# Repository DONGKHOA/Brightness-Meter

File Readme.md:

# BRIGHTNESS METER
## Yêu cầu hệ thống
- Thiết kế máy đo độ rọi ánh sáng sử dụng LDR: có 2 thang đo
  - Thang 1: tầm đo 10-100lux, độ phân giải 1lux
  - Thang 2: tầm đo 10-1000lux, độ phân giải 10lux
  - Màn hình hiển thị LCD giá trị đo được, có nút nhấn để thay đổi giữa 2 thang đo
  - Mạch cho phép cài đặt giá trị ngưỡng độ rọi thông qua LCD và nút nhấn. Nếu độ rọi đặt vào máy đo lớn hơn giá trị cài đặt, báo đỏ LED.

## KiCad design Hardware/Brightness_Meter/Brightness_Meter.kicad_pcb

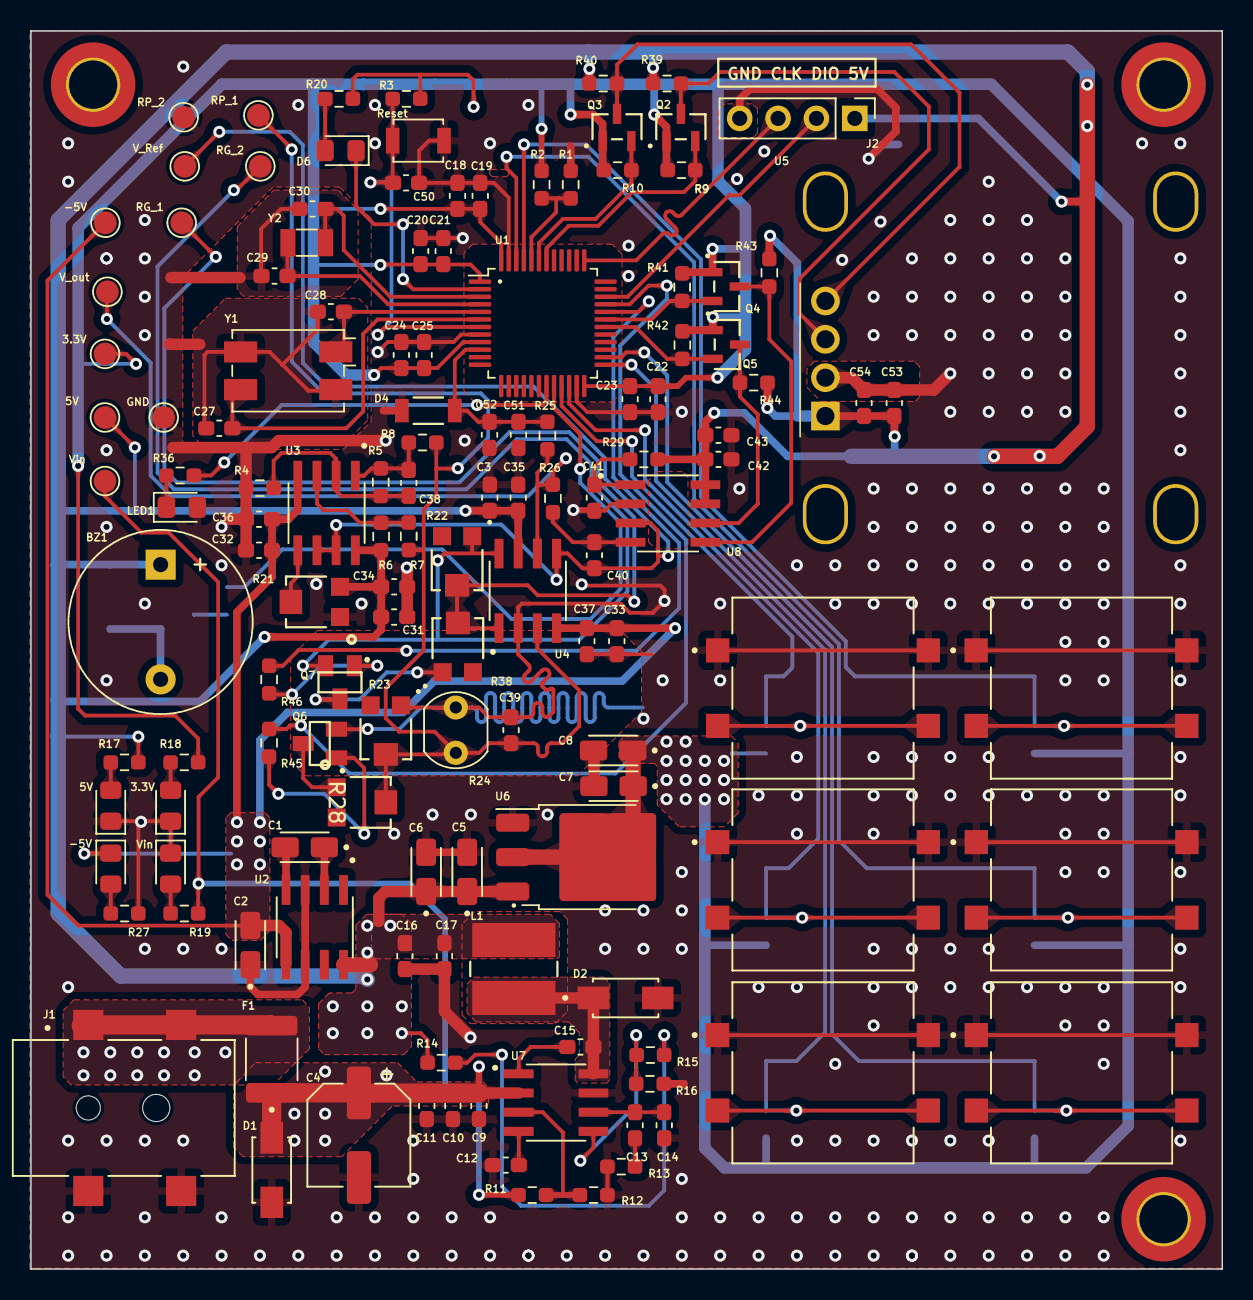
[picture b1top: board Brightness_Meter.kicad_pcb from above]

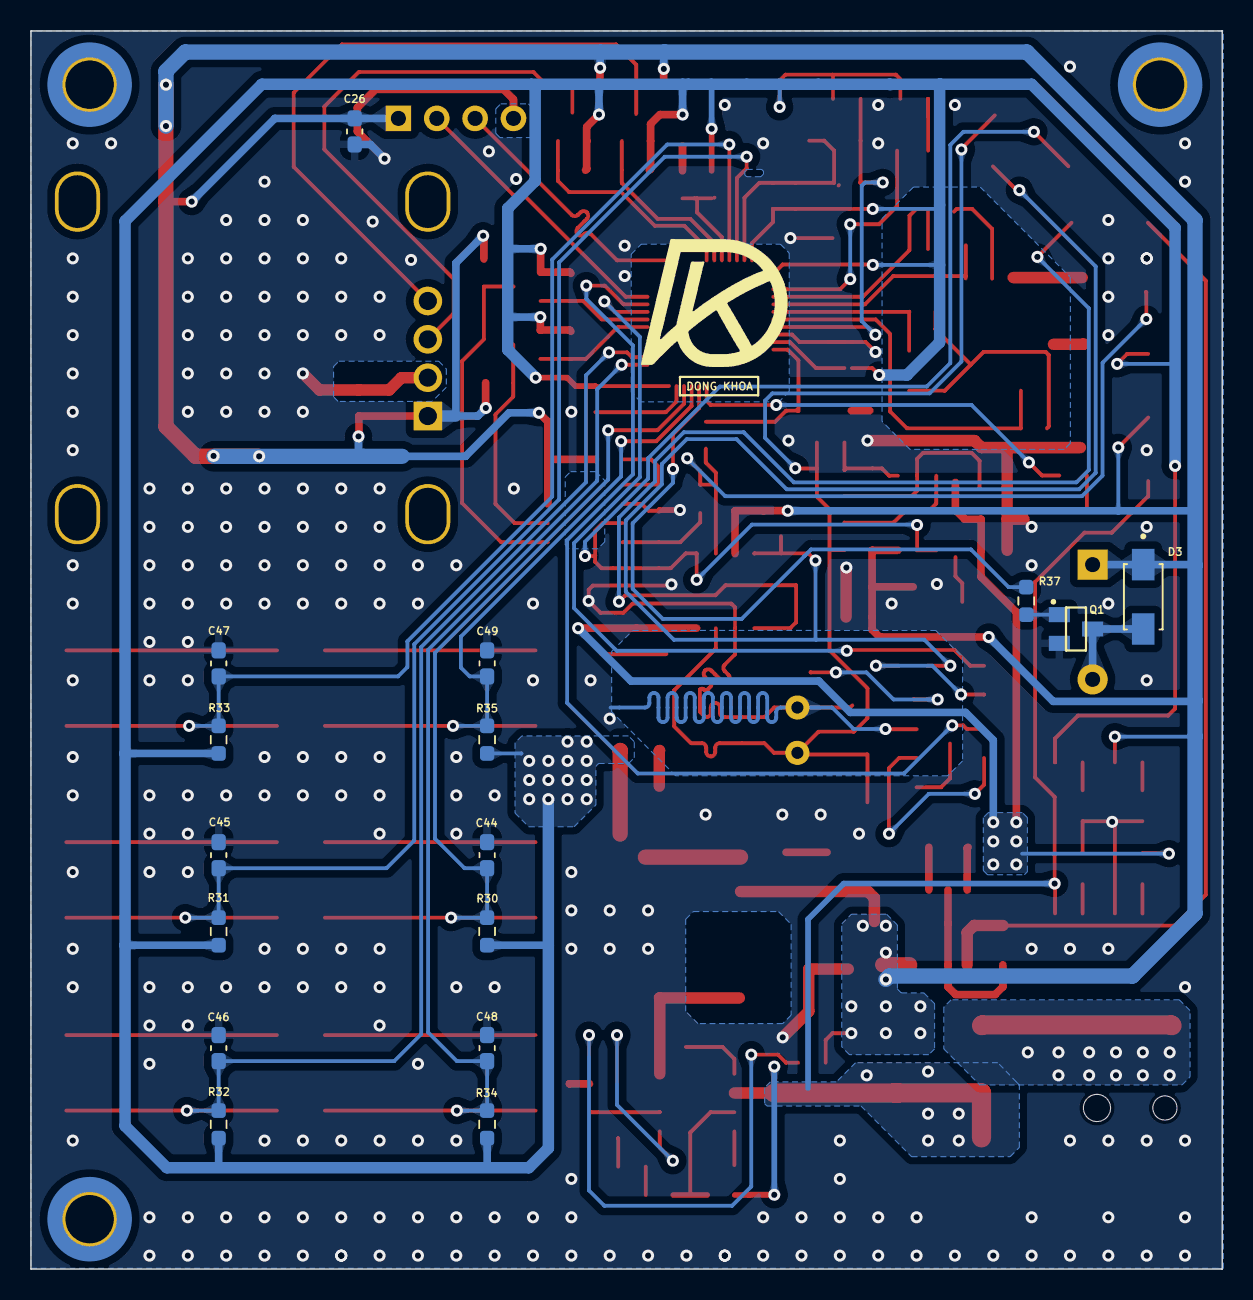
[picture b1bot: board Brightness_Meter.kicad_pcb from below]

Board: 2 copper layers, 78.9 x 82.0 mm, 153 parts (16 on the bottom side), 67 nets.

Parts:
3.3V: 3.3V; TestPoint_Pad_D1.5mm
3.3V#2, 5V#2: BLUE; LED_0805_2012Metric_Pad1.15x1.40mm_HandSolder
5V: 5V; TestPoint_Pad_D1.5mm
-5V: -5V; TestPoint_Pad_D1.5mm
-5V#2: BLUE; LED_0805_2012Metric_Pad1.15x1.40mm_HandSolder
BZ1: Buzzer; Buzzer_12x9.5RM7.6
C1, C2, C6, C7: 10uF/16V; CAPMP3216X180N
C3, C26, C31, C32, C33, C51: 10uF/16V; C_0603_1608Metric_Pad1.08x0.95mm_HandSolder
C4: 22uF/25V; CP_Elec_6.3x5.4
C5, C8: 1uF/25V; CAPMP3216X180N
C9, C10: 4.7uF/25V; C_0603_1608Metric_Pad1.08x0.95mm_HandSolder
C11, C12, C25: 10nF/50V; C_0603_1608Metric_Pad1.08x0.95mm_HandSolder
C13: 1nF/50V; C_0603_1608Metric_Pad1.08x0.95mm_HandSolder
C14: 47pF/50V; C_0603_1608Metric_Pad1.08x0.95mm_HandSolder
C15: 0.1uF/16V; C_0603_1608Metric_Pad1.08x0.95mm_HandSolder
C16, C17: 47uF/6.3V; C_0603_1608Metric_Pad1.08x0.95mm_HandSolder
C18, C20, C22: 4.7uF/10V; C_0603_1608Metric_Pad1.08x0.95mm_HandSolder
C19, C21, C23, C34, C35, C36, C37, C44, C45, C46, C47, C48, C49, C50, C52: 100nF/16V; C_0603_1608Metric_Pad1.08x0.95mm_HandSolder
C24, C39: 1uF/16V; C_0603_1608Metric_Pad1.08x0.95mm_HandSolder
C27, C28, C29, C30: 20pF/50V; C_0603_1608Metric_Pad1.08x0.95mm_HandSolder
C38: 10pF/50V; C_0603_1608Metric_Pad1.08x0.95mm_HandSolder
C40, C41, C43, C54: 100nF/50V; C_0603_1608Metric_Pad1.08x0.95mm_HandSolder
C42, C53: 10uF/6.3V; C_0603_1608Metric_Pad1.08x0.95mm_HandSolder
D1, D2, D3: SS34; DIOM4325X250N
D4: ZMM3V3; ZDO_ZMM_3p5x1p45_STM
D6: Led_test; LED_0805_2012Metric_Pad1.15x1.40mm_HandSolder
DOWN1: DOWN; SW_TL3300CF260Q
F1: Fuse_Small; Fuse_1812_4532Metric_Pad1.30x3.40mm_HandSolder
GND: GND; TestPoint_Pad_D1.5mm
H1, H2, H3: MountingHole; MountingHole_3.2mm_M3_DIN965_Pad_TopBottom
J1: JACK-DC; SPARKFUN_PRT-12748
J2: Load Program; PinHeader_1x04_P2.54mm_Vertical
L1: 6.8uH/2.2A; IND_SDE0604A_5P8X5P2X4P5_BRN
LED1: RED; LED_0805_2012Metric_Pad1.15x1.40mm_HandSolder
LEFT1: LEFT; SW_TL3300CF260Q
MODE1: MODE; SW_TL3300CF260Q
Q1, Q6, Q7: MMBT2222A; SOT23
Q2, Q3, Q4, Q5: BSN20; SOT23_NEX
R1, R2, R25, R26: 0/1%; R_0603_1608Metric_Pad0.98x0.95mm_HandSolder
R3, R9, R10, R16, R30, R31, R32, R33, R34, R35, R39, R40, R41, R42, R43, R44: 10k/1%; R_0603_1608Metric_Pad0.98x0.95mm_HandSolder
R4, R5, R6, R7, R8: R_Small_US; R_0603_1608Metric_Pad0.98x0.95mm_HandSolder
R11: 330k/1%; R_0603_1608Metric_Pad0.98x0.95mm_HandSolder
R12: 47k/1%; R_0603_1608Metric_Pad0.98x0.95mm_HandSolder
R13: 30k/1%; R_0603_1608Metric_Pad0.98x0.95mm_HandSolder
R14: 2.49k/1%; R_0603_1608Metric_Pad0.98x0.95mm_HandSolder
R15: 49.9k/1%; R_0603_1608Metric_Pad0.98x0.95mm_HandSolder
R17, R18, R20, R36, R37, R45, R46: 1k/1%; R_0603_1608Metric_Pad0.98x0.95mm_HandSolder
R19, R27: 4.7k/1%; R_0603_1608Metric_Pad0.98x0.95mm_HandSolder
R21: EVM-3ESX50B14; EVM-3ESX50B14_PAN
R22, R23, R28, R38: EVM-3E; EVM-3ESX50B14_PAN
R24: GL5528; R_LDR_5.0x4.1mm_P3mm_Vertical
R29: 220/1%; R_0603_1608Metric_Pad0.98x0.95mm_HandSolder
RG_1, RG_2: RG; TestPoint_Pad_D1.5mm
RIGHT1: RIGHT; SW_TL3300CF260Q
RP_1, RP_2: RP; TestPoint_Pad_D1.5mm
Reset: SW_Push; SW_SPST_B3U-1000P
SET1: SET; SW_TL3300CF260Q
U1: STM32F030C8Tx; LQFP-48_7x7mm_P0.5mm
U2: ICL7662CPA; SOIC127P600X175-8N
U3: MCP6002; SOIC127P599X173-8N
U4: INA128; SOIC127P599X175-8N
U5: SSD1306
U6: LM1117DT-3.3; TO-252-3_TabPin2
U7: TPS54331D; SOIC127P599X175-8N
U8: HX710B
UP1: UP; SW_TL3300CF260Q
V_Ref: V_Ref; TestPoint_Pad_D1.5mm
V_out: V_out; TestPoint_Pad_D1.5mm
Vin: BLUE; LED_0805_2012Metric_Pad1.15x1.40mm_HandSolder
Vin#2: Vin; TestPoint_Pad_D1.5mm
Y1: 8MHz; Crystal_SMD_EuroQuartz_MQ-4Pin_7.0x5.0mm
Y2: 32.768KHz; Crystal_SMD_3215-2Pin_3.2x1.5mm

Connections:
+3.3V: 3.3V.1, C7.1, C8.1, C18.1, C19.1, C20.1, C21.1, C22.1, C23.1, C24.1, C25.1, Q2.1 (G), Q3.1 (G), Q4.1 (G), Q5.1 (G), R2.1, R3.1, R9.1, R10.1, R18.1, R20.1, R30.2, R31.2, R32.2, R33.2, R34.2, R35.2, R41.1, R42.1, U1.1 (VDD), U1.9 (VDDA), U1.24 (VDD), U1.48 (VDD), U6.2 (VO)
+5V: 5V.1, BZ1.1 (-), C3.1, C5.1, C6.1, C16.1, C17.1, C26.1, C31.1, C34.1, C35.1, C42.1, C43.1, C53.1, C54.1, D3.C, J2.1, L1.1, R6.2, R14.1, R17.1, R21.3, R29.2, R39.1, R40.1, R43.1, R44.1, U2.8 (V+), U3.8 (VDD), U4.7 (V+), U5.1 (vcc), U6.3 (VI), U8.7 (DVDD), U8.8 (AVDD)
-5V: -5V.1, -5V#2.1 (K), C2.2, C32.2, C33.2, C36.2, C37.2, U2.5 (VOUT), U3.4 (VSS), U4.4 (V-)
/MCU/BOOT0: R1.1, R2.2, U1.44 (BOOT0)
/MCU/LED_TEST: D6.1 (K), U1.2 (PC13)
/MCU/OSC32_IN: C30.1, U1.3 (PC14), Y2.1
/MCU/OSC32_OUT: C29.1, U1.4 (PC15), Y2.2
/MCU/OSC_IN: C28.1, U1.5 (PF0), Y1.1
/MCU/OSC_OUT: C27.1, U1.6 (PF1), Y1.3
/MCU/RESET: C50.2, R3.2, Reset.2, U1.7 (NRST)
/MCU/SWCLK: J2.3, U1.37 (PA14)
/MCU/SWDIO: J2.2, U1.34 (PA13)
/Power/Vin: C4.1, C9.1, C10.1, C11.1, D1.C, F1.2, R11.1, R19.1, U7.2 (VIN), Vin#2.1
/measure/CURRENT_SRC: C39.2, R7.1, R8.2, R23.2, R24.1, R28.2, RP_1.1, U4.3 (+)
/measure/vout: R25.2, R26.1, U4.6, V_out.1
ADC_CLK: Q4.2 (S), R41.2, U1.31 (PA10)
ADC_DATA: Q5.2 (S), R42.2, U1.30 (PA9)
ADC_HX71OB: C40.2, R26.2, U8.4 (INP)
ADC_INO: C51.1, C52.1, D4.1, R25.1, U1.10 (PA0)
BUZZER: R37.1, U1.20 (PB2)
CHANGE_GAIN: R46.2, U1.32 (PA11)
CHANGE_RESISTOR: R45.2, U1.33 (PA12)
CLK_HX710B: Q4.3 (D), R43.2, U8.5 (PD_SCK)
DATA_HX710B: Q5.3 (D), R44.2, U8.6 (DOUT)
GND: 3.3V#2.1 (K), 5V#2.1 (K), C2.1, C3.2, C4.2, C5.2, C6.2, C7.2, C8.2, C9.2, C10.2, C11.2, C12.2, C14.2, C16.2, C17.2, C18.2, C19.2, C20.2, C21.2, C22.2, C23.2, C24.2, C25.2, C26.2, C27.2, C28.2, C29.2, C30.2, C31.2, C32.1, C33.1, C34.2, C35.2, C36.1, C37.1, C39.1, C41.1, C42.2, C43.2, C44.1, C45.1, C46.1, C47.1, C48.1, C49.1, C50.1, C51.2, C52.2, C53.2, C54.2, D1.A, D2.A, D4.2, DOWN1.1, DOWN1.2, GND.1, J1.2, J1.3, J2.4, LED1.2 (A), LEFT1.1, LEFT1.2, MODE1.1, MODE1.2, Q1.2, Q6.2, R1.2, R4.2, R12.2, R13.2, R16.2, R21.1, R23.1, R24.2, R27.2, RIGHT1.1, RIGHT1.2, RP_2.1, Reset.1, SET1.1, SET1.2, U1.8 (VSSA), U1.23 (VSS), U1.47 (VSS), U2.3 (GND), U2.6 (LV), U4.2 (-), U5.2 (gnd), U6.1 (GND), U7.7 (GND), U8.2 (AGND), UP1.1, UP1.2, Vin.1 (K), Y1.2, Y1.4
I2C_SCL: Q2.2 (S), R9.2, U1.42 (PB6)
I2C_SDA: Q3.2 (S), R10.2, U1.43 (PB7)
LED_INFO: R36.2, U1.19 (PB1)
unnamed: 3.3V#2.2 (A), R18.2
unnamed: 5V#2.2 (A), R17.2
unnamed: -5V#2.2 (A), R27.1
unnamed: BZ1.2 (+), D3.A, Q1.3
unnamed: C13.2, R13.1
unnamed: D6.2 (A), R20.2
unnamed: F1.1, J1.1_1, J1.1_2
unnamed: LED1.1 (K), R36.1
unnamed: Q1.1, R37.2
unnamed: Q6.1, R45.1
unnamed: Q6.3, R28.1
unnamed: Q7.1, R46.1
unnamed: Q7.2, R22.1, RG_2.1, U4.8 (Rg)
unnamed: Q7.3, R38.1
unnamed: R14.2, R15.1
unnamed: R22.2, R38.2, RG_1.1, U4.1 (Rg)
unnamed: C1.1, U2.2 (CAP+)
unnamed: C1.2, U2.4 (CAP-)
unnamed: R6.1, R7.2, U3.3 (VINA+)
unnamed: C38.1, R4.1, R5.2, U3.2 (VINA-)
unnamed: R21.2, U3.5 (VINB+)
unnamed: C38.2, R5.1, R8.1, U3.1 (VOUTA)
unnamed: C15.2, U7.1 (BOOT)
unnamed: C13.1, C14.1, U7.6 (COMP)
unnamed: R11.2, R12.1, U7.3 (EN)
unnamed: C15.1, D2.C, L1.2, U7.8 (PH)
unnamed: C12.1, U7.4 (SS)
unnamed: R15.2, R16.1, U7.5 (VSENSE)
unnamed: C41.2, R29.1, U8.1 (VREF)
unnamed: R19.2, Vin.2 (A)
SCL_SSD1306: Q2.3 (D), R39.2, U5.3 (scl)
SDA_SSD1306: Q3.3 (D), R40.2, U5.4 (sda)
SW_DOWN: C45.2, DOWN1.3, DOWN1.4, R31.1, U1.46 (PB9)
SW_LEFT: C46.2, LEFT1.3, LEFT1.4, R32.1, U1.26 (PB13)
SW_MODE: C49.2, MODE1.3, MODE1.4, R35.1, U1.21 (PB10)
SW_RIGHT: C47.2, R33.1, RIGHT1.3, RIGHT1.4, U1.45 (PB8)
SW_SET: C48.2, R34.1, SET1.3, SET1.4, U1.25 (PB12)
SW_UP: C44.2, R30.1, U1.22 (PB11), UP1.3, UP1.4
VREF: C40.1, U3.6 (VINB-), U3.7 (VOUTB), U4.5 (Ref), U8.3 (INN), V_Ref.1

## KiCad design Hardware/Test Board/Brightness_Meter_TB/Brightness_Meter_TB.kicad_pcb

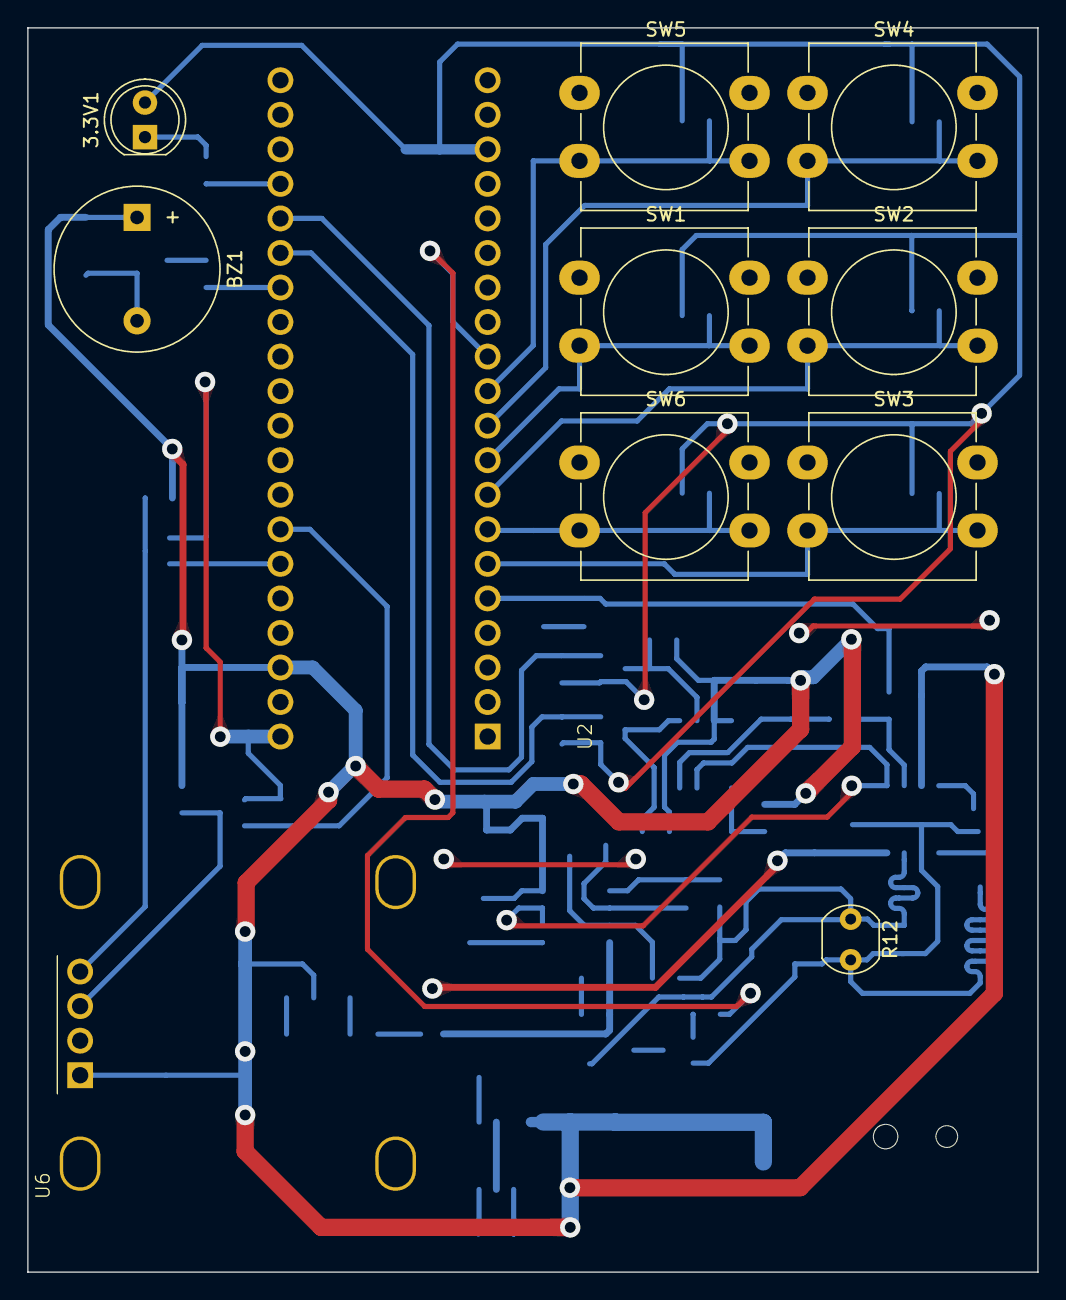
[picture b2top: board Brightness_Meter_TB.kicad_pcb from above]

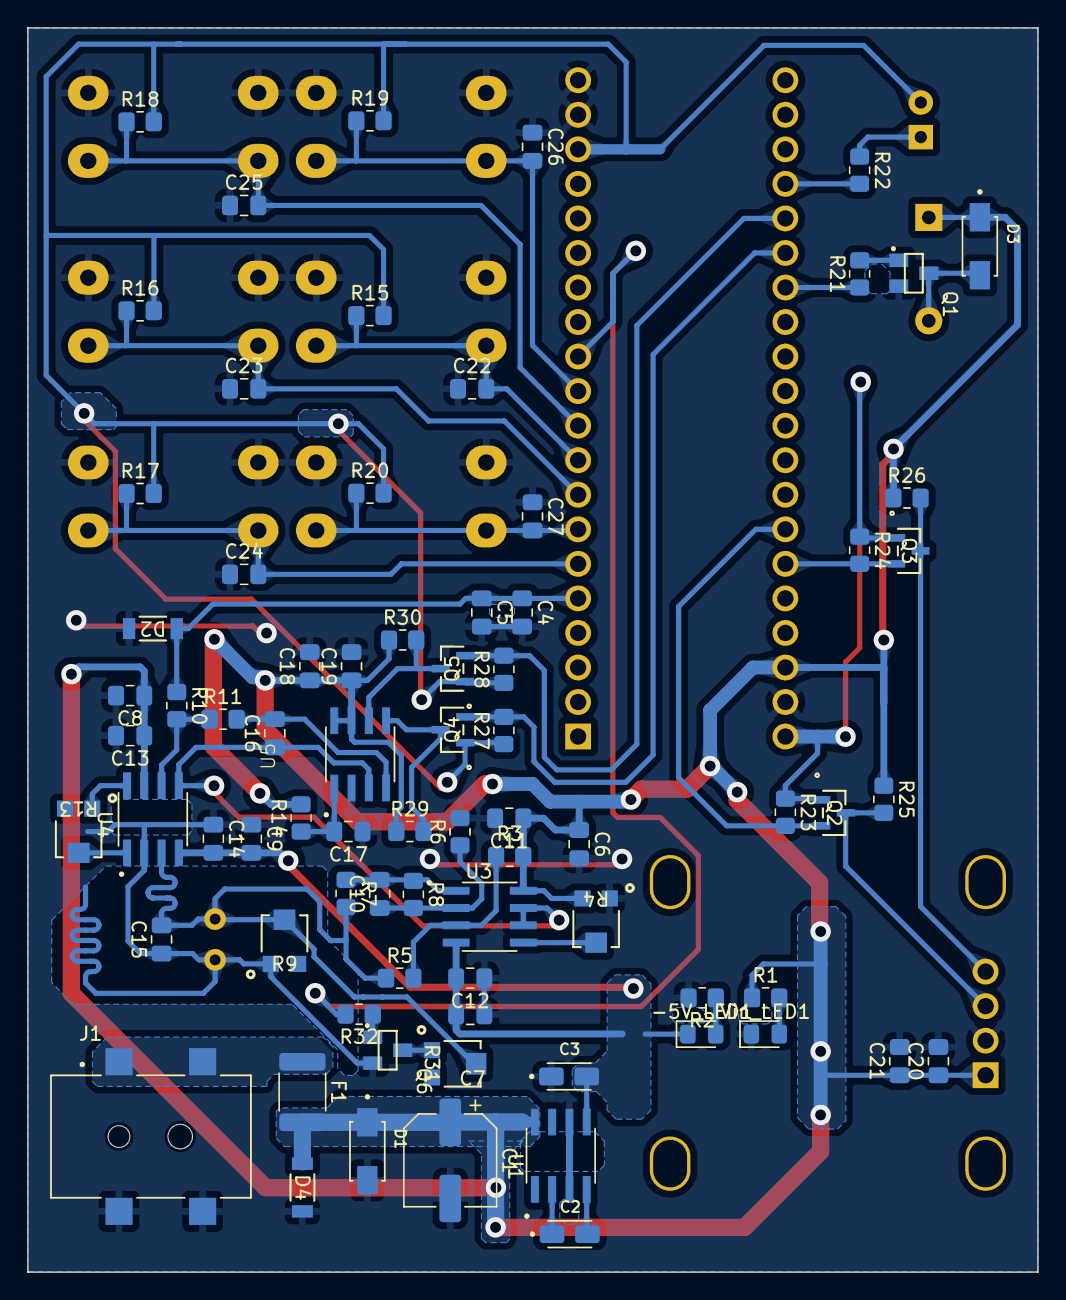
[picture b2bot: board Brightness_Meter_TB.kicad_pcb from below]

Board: 2 copper layers, 74.3 x 91.5 mm, 87 parts (76 on the bottom side), 43 nets.

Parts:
3.3V1: RED; LED_D5.0mm
-5V_LED1: BLUE; LED_0805_2012Metric_Pad1.15x1.40mm_HandSolder
BZ1: Buzzer; Buzzer_12x9.5RM7.6
C1: 22uF/25V; CP_Elec_6.3x5.4
C2, C3: 10uF/16V; CAPMP3216X180N
C4, C11, C12, C13, C14, C16, C17, C19, C20, C22, C23, C24, C25, C26, C27: 100nF/50V; C_0805_2012Metric_Pad1.18x1.45mm_HandSolder
C5, C6, C7, C8, C9, C18, C21: 10uF/6.3V; C_0805_2012Metric_Pad1.18x1.45mm_HandSolder
C10: 10pF/50V; C_0805_2012Metric_Pad1.18x1.45mm_HandSolder
C15: 1uF/16V; C_0805_2012Metric_Pad1.18x1.45mm_HandSolder
D1, D3: SS34; DIOM4325X250N
D2: ZMM3V3; ZDO_ZMM_3p5x1p45_STM
D4: ZMM5V1; ZDO_ZMM_3p5x1p45_STM
F1: Fuse_Small; Fuse_1812_4532Metric_Pad1.30x3.40mm_HandSolder
J1: JACK-DC; SPARKFUN_PRT-12748
Q1, Q6: MMBT2222A; SOT23
Q2, Q3, Q4, Q5: BSN20; SOT23_NEX
R1, R2: 4.7k/1%; R_0805_2012Metric_Pad1.20x1.40mm_HandSolder
R3, R5, R6, R7, R8: R_Small_US; R_0805_2012Metric_Pad1.20x1.40mm_HandSolder
R4: EVM-3ESX50B14; EVM-3ESX50B14_PAN
R9, R13, R31: EVM-3E; EVM-3ESX50B14_PAN
R10, R11: 0/1%; R_0805_2012Metric_Pad1.20x1.40mm_HandSolder
R12: GL5528; R_LDR_5.0x4.1mm_P3mm_Vertical
R14: 220/1%; R_0805_2012Metric_Pad1.20x1.40mm_HandSolder
R15, R16, R17, R18, R19, R20, R23, R24, R25, R26, R27, R28, R29, R30: 10k/1%; R_0805_2012Metric_Pad1.20x1.40mm_HandSolder
R21, R22, R32: 1k/1%; R_0805_2012Metric_Pad1.20x1.40mm_HandSolder
SW1: UP; SW_PUSH-12mm_Wuerth-430476085716
SW2: DOWN; SW_PUSH-12mm_Wuerth-430476085716
SW3: LEFT; SW_PUSH-12mm_Wuerth-430476085716
SW4: RIGHT; SW_PUSH-12mm_Wuerth-430476085716
SW5: SET; SW_PUSH-12mm_Wuerth-430476085716
SW6: MODE; SW_PUSH-12mm_Wuerth-430476085716
U1: ICL7662CPA; SOIC127P600X175-8N
U2: STM32F103C8T6; STM32F103C8T6_BP
U3: MCP6002; SOIC127P599X173-8N
U4: INA128; SOIC127P599X175-8N
U5: HX710B
U6: SSD1306
Vin_LED1: BLUE; LED_0805_2012Metric_Pad1.15x1.40mm_HandSolder

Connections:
+3.3V: 3.3V1.2 (A), Q2.1 (G), Q3.1 (G), Q4.1 (G), Q5.1 (G), R15.2, R16.2, R17.2, R18.2, R19.2, R20.2, R23.1, R24.1, R27.1, R28.1, U2.1 (VBAT), U2.18 (3V3), U2.40 (3V3)
+5V: BZ1.1 (-), C1.1, C6.1, C8.1, C11.1, C13.1, C18.1, C19.1, C20.1, C21.1, D1.C, D3.C, D4.1, F1.2, R1.1, R3.2, R4.3, R14.2, R25.1, R26.1, R29.1, R30.1, U1.8 (V+), U2.38 (5V), U3.8 (VDD), U4.7 (V+), U5.7 (DVDD), U5.8 (AVDD), U6.1 (vcc)
-5V: -5V_LED1.1 (K), C3.2, C7.2, C9.2, C12.2, C14.2, U1.5 (VOUT), U3.4 (VSS), U4.4 (V-)
/Measure/CURRENT_SRC: C15.2, R5.1, R7.2, R9.2, R12.1, R31.2, U4.3 (+)
/Measure/vout: R10.2, R11.1, U4.6
ADC_CLK: Q4.2 (S), R27.2, U2.26 (PA9)
ADC_DATA: Q5.2 (S), R28.2, U2.25 (PA8)
ADC_HX71OB: C16.2, R11.2, U5.4 (INP)
ADC_INO: C4.1, C5.1, D2.1, R10.1, U2.5 (PA0)
BUZZER: R21.1, U2.27 (PA10)
CHANGE_RESISTOR: R32.2, U2.12 (PA7)
CLK_HX710B: Q4.3 (D), R29.2, U5.5 (PD_SCK)
DATA_HX710B: Q5.3 (D), R30.2, U5.6 (DOUT)
GND: C1.2, C3.1, C4.2, C5.2, C6.2, C7.1, C8.2, C9.1, C11.2, C12.1, C13.2, C14.1, C15.1, C17.1, C18.2, C19.2, C20.2, C21.2, C22.1, C23.1, C24.1, C25.1, C26.1, C27.1, D1.A, D2.2, D4.2, J1.2, J1.3, Q1.2, Q6.2, R2.2, R4.1, R6.2, R9.1, R12.2, SW1.1, SW2.1, SW3.1, SW4.1, SW5.1, SW6.1, U1.3 (GND), U1.6 (LV), U2.19 (GND), U2.20 (GND), U2.39 (GND), U4.2 (-), U5.2 (AGND), U6.2 (gnd), Vin_LED1.1 (K)
I2C_SCL: Q2.2 (S), R23.2, U2.34 (PB6)
I2C_SDA: Q3.2 (S), R24.2, U2.35 (PB7)
LED_INFO: R22.2, U2.24 (PB15)
unnamed: 3.3V1.1 (K), R22.1
unnamed: -5V_LED1.2 (A), R2.1
unnamed: BZ1.2 (+), D3.A, Q1.3
unnamed: F1.1, J1.1_1, J1.1_2
unnamed: Q1.1, R21.2
unnamed: Q6.1, R32.1
unnamed: Q6.3, R31.1
unnamed: R13.1, U4.8 (Rg)
unnamed: R13.2, U4.1 (Rg)
unnamed: C2.1, U1.2 (CAP+)
unnamed: C2.2, U1.4 (CAP-)
unnamed: R3.1, R5.2, U3.3 (VINA+)
unnamed: C10.1, R6.1, R8.2, U3.2 (VINA-)
unnamed: R4.2, U3.5 (VINB+)
unnamed: C10.2, R7.1, R8.1, U3.1 (VOUTA)
unnamed: C17.2, R14.1, U5.1 (VREF)
unnamed: R1.2, Vin_LED1.2 (A)
SCL_SSD1306: Q2.3 (D), R25.2, U6.3 (scl)
SDA_SSD1306: Q3.3 (D), R26.2, U6.4 (sda)
SW_DOWN: C23.2, R16.1, SW2.2, U2.8 (PA3)
SW_LEFT: C24.2, R17.1, SW3.2, U2.6 (PA1)
SW_MODE: C27.2, R20.1, SW6.2, U2.7 (PA2)
SW_RIGHT: C25.2, R18.1, SW4.2, U2.10 (PA5)
SW_SET: C26.2, R19.1, SW5.2, U2.11 (PA6)
SW_UP: C22.2, R15.1, SW1.2, U2.9 (PA4)
VREF: C16.1, U3.6 (VINB-), U3.7 (VOUTB), U4.5 (Ref), U5.3 (INN)

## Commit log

2023-12-06 upload folder
2024-01-15 upload hardware
2024-02-07 final commit
